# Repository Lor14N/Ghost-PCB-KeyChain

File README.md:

# Ghost-PCB-KeyChain
PCB Keychain following Solder.hackclub's tutorial.
--------------------------------------------------
Bill of Materials:
  
  Reference: BT2
  Quantity: 1
  Value: Battery
  Footprint: BatteryHolder_Keystone_3034_1x20mm
  Datasheet: ~

  Reference: C1, C2
  Quantity: 2
  Value: C
  Footprint: CP_Radial_D8.0mm_P5.00mm
  Datasheet: ~
  
  Reference: D1, D3, D4, D5, D7, D8, D9
  Quantity: 7
  Value: LED
  Footprint: LED_D5.0mm
  Datasheet: ~
  
  Reference: Q1, Q2
  Quantity: 2
  Value: BC107
  Footprint: TO-18-3
  Datasheet: http://www.b-kainka.de/Daten/Transistor/BC108.pdf
  
  Reference: R1, R2, R3, R4
  Quantity: 4
  Value: R
  Footprint: R_Axial_DIN0207_L6.3mm_D2.5mm_P7.62mm_Horizontal
  Datasheet: ~

Slack Username: Lor14N

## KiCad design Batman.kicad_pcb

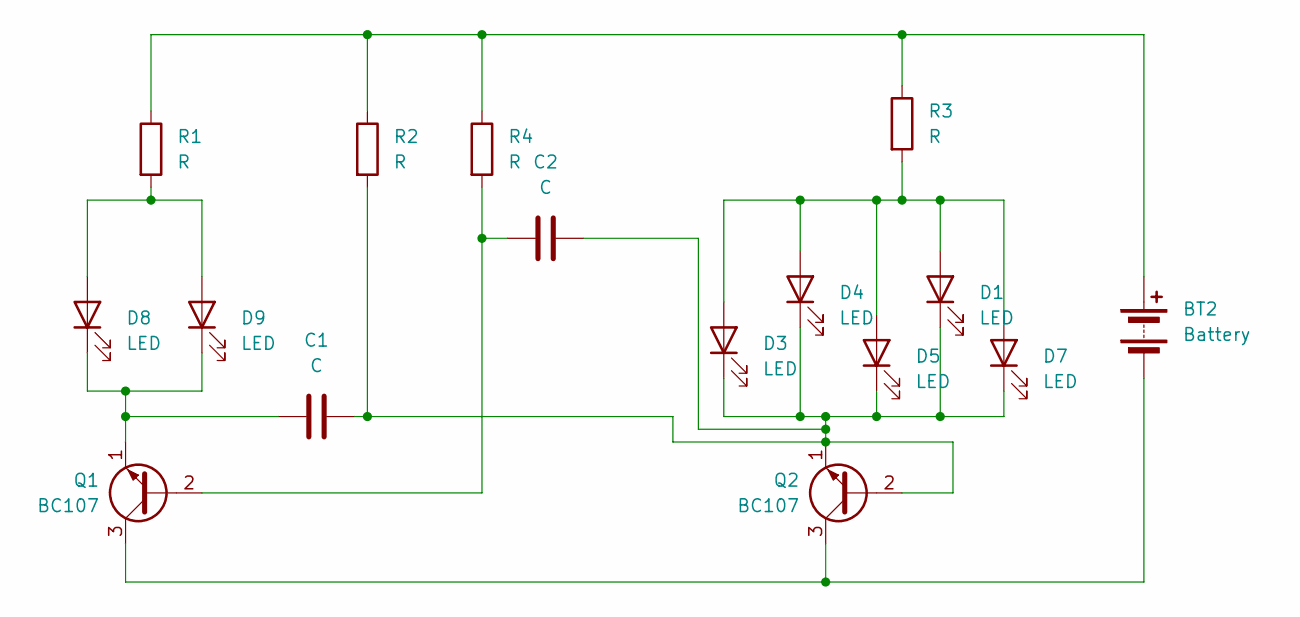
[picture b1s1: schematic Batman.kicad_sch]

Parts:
BT2: Battery; BatteryHolder_Keystone_3034_1x20mm
C1, C2: C; CP_Radial_D8.0mm_P5.00mm
D1, D3, D4, D5, D7, D8, D9: LED; LED_D5.0mm
Q1, Q2: BC107; TO-18-3
R1, R2, R3, R4: R; R_Axial_DIN0207_L6.3mm_D2.5mm_P7.62mm_Horizontal

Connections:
unnamed: BT2.1 (+), R1.1, R2.1, R3.1, R4.1
unnamed: BT2.2 (-), Q1.3 (C), Q2.3 (C)
unnamed: D1.2 (A), D3.2 (A), D4.2 (A), D5.2 (A), D7.2 (A), R3.2
unnamed: C1.2, C2.2, D1.1 (K), D3.1 (K), D4.1 (K), D5.1 (K), D7.1 (K), Q2.1 (E), Q2.2 (B), R2.2
unnamed: D8.2 (A), D9.2 (A), R1.2
unnamed: C1.1, D8.1 (K), D9.1 (K), Q1.1 (E)
unnamed: C2.1, Q1.2 (B), R4.2

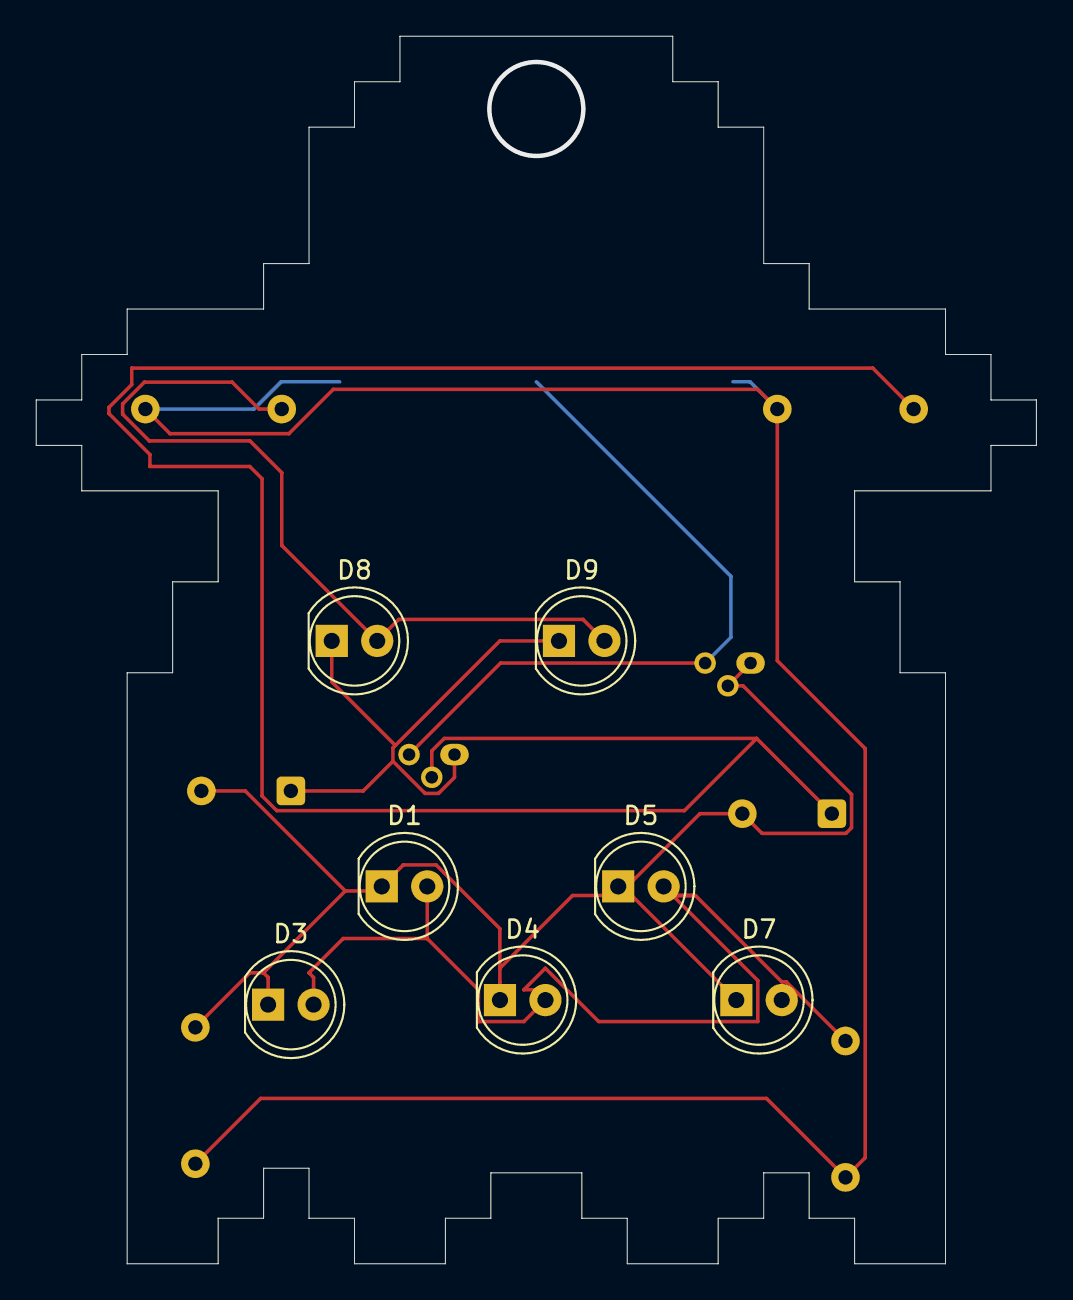
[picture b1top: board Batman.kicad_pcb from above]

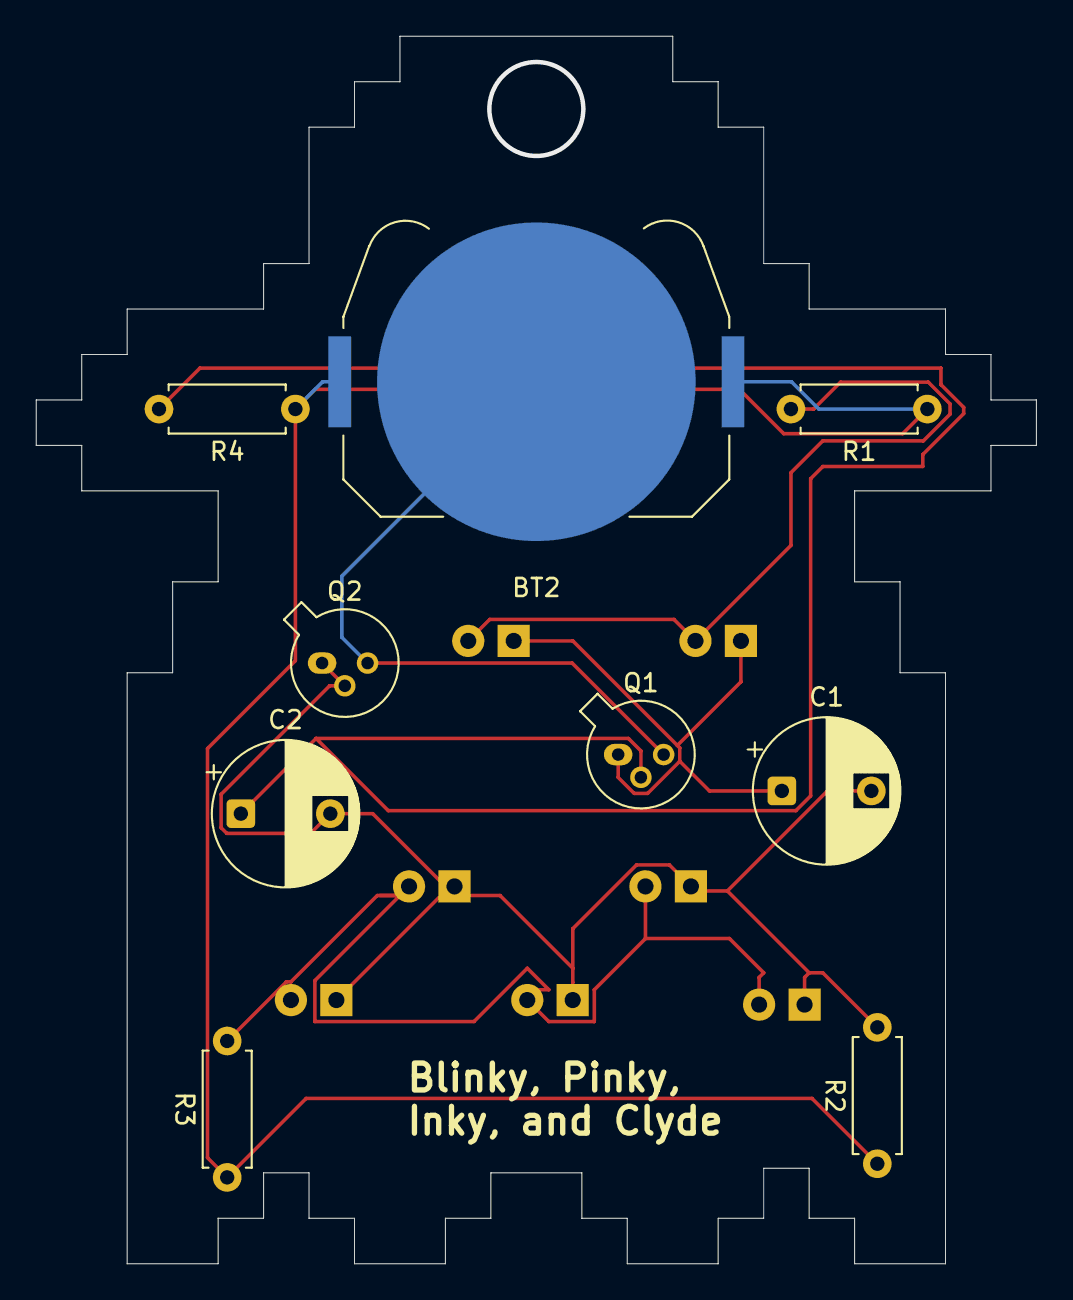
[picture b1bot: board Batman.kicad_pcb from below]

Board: 2 copper layers, 55.9 x 68.6 mm, 16 parts (9 on the bottom side), 7 nets.

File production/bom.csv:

Designator,Footprint,Quantity,Value,LCSC Part #
BT2,BatteryHolder_Keystone_3034_1x20mm,1,Battery,
"C1, C2",CP_Radial_D8.0mm_P5.00mm,2,C,
"D1, D3, D4, D5, D7, D8, D9",LED_D5.0mm,7,LED,
"Q1, Q2",TO-18-3,2,BC107,
"R1, R2, R3, R4",R_Axial_DIN0207_L6.3mm_D2.5mm_P7.62mm_Horizontal,4,R,

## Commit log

2025-07-07 Source
2025-07-07 Create Source
